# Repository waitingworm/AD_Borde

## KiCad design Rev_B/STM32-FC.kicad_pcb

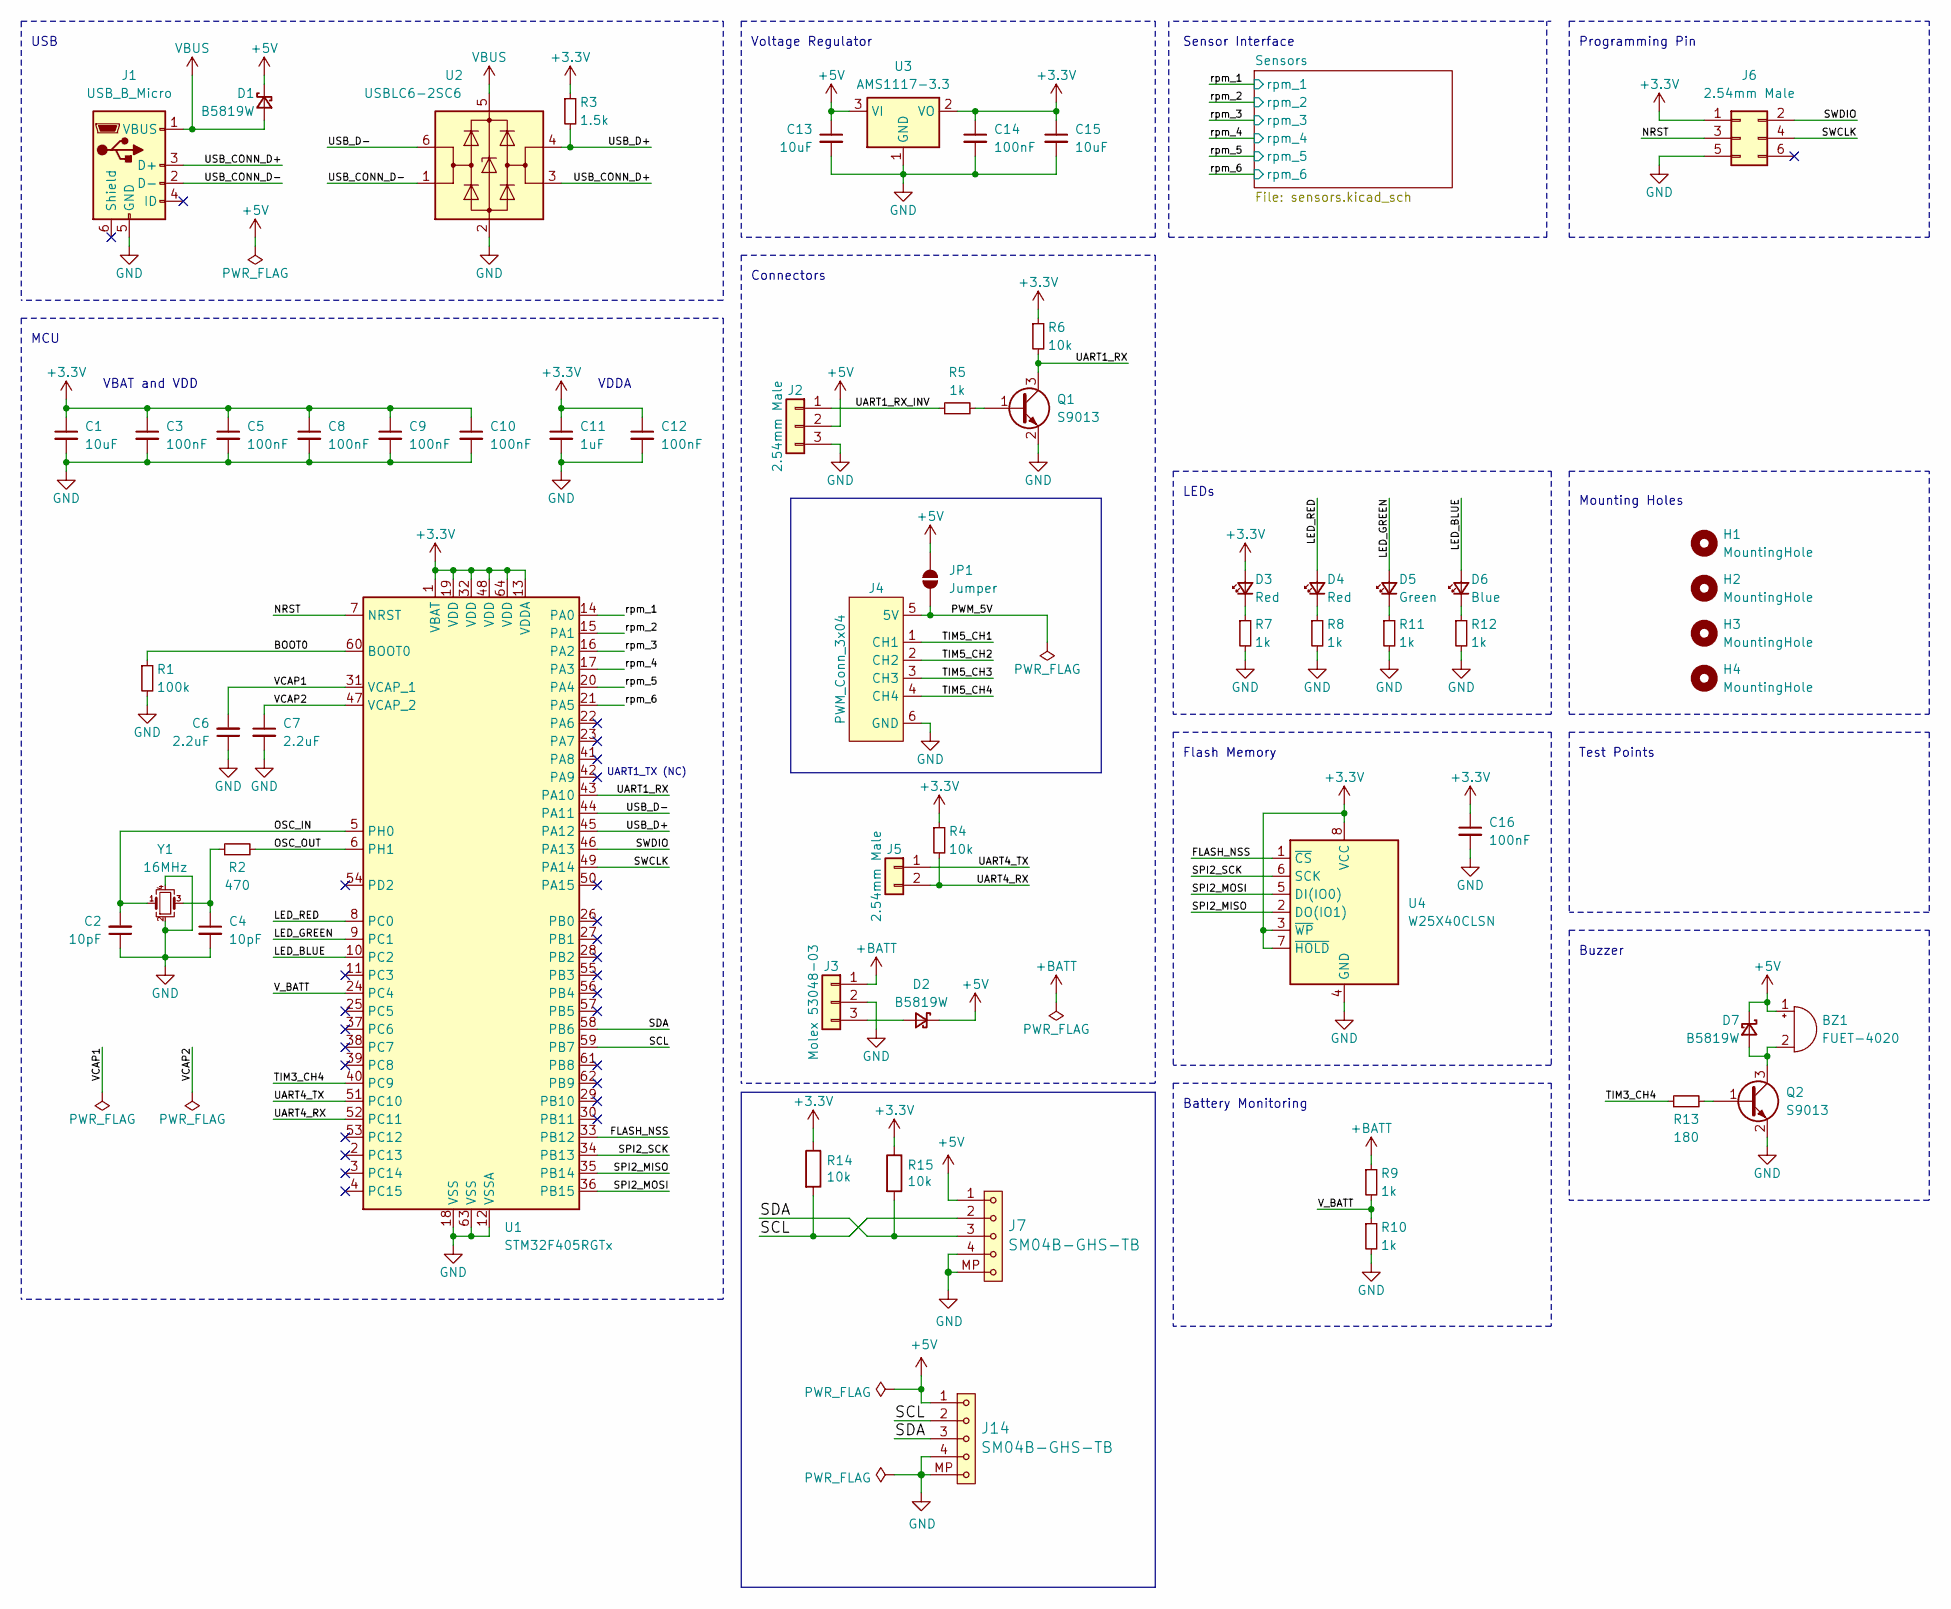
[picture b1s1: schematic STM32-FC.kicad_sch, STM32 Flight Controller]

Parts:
BZ1: FUET-4020
C1: 10uF; C_0402_1005Metric; LCSC C19702
C2, C4: 10pF; C_0402_1005Metric
C3, C5, C8, C9, C10, C12: 100nF; C_0402_1005Metric; LCSC C1525
C6, C7: 2.2uF; C_0402_1005Metric
C11: 1uF; C_0402_1005Metric; LCSC C1525
C13, C15: 10uF; C_0402_1005Metric
C14, C16: 100nF; C_0402_1005Metric
D1, D2: B5819W; D_SOD-123; LCSC C8598
D3, D4: Red; LED_0603_1608Metric
D5: Green; LED_0603_1608Metric
D6: Blue; LED_0603_1608Metric
D7: B5819W; D_SOD-123
H1, H2, H3, H4: MountingHole; MountingHole_3.2mm_M3
J1: USB_B_Micro; USB_Micro-B_Molex-105017-0001
J2: 2.54mm Male; PinHeader_1x03_P2.54mm_Vertical
J3: Molex 53048-03; Molex_PicoBlade_53048-0310_1x03_P1.25mm_Horizontal
J4: PWM_Conn_3x04
J5: 2.54mm Male; PinHeader_1x02_P2.54mm_Vertical
J6: 2.54mm Male; PinHeader_2x03_P2.54mm_Vertical
J7, J14: SM04B-GHS-TB; JST_GH_SM04B-GHS-TB_1x04-1MP_P1.25mm_Horizontal
JP1: Jumper; SolderJumper-2_P1.3mm_Open_TrianglePad1.0x1.5mm
Q1, Q2: S9013; SOT-23-3
R1: 100k; R_0402_1005Metric
R2: 470; R_0402_1005Metric
R3: 1.5k; R_0402_1005Metric
R4, R6: 10k; R_0402_1005Metric
R5, R7, R8, R9, R10, R11, R12: 1k; R_0402_1005Metric
R13: 180; R_0402_1005Metric
R14, R15: 10k; R_0603_1608Metric
U1: STM32F405RGTx; LQFP-64_10x10mm_P0.5mm
U2: USBLC6-2SC6; SOT-23-6
U3: AMS1117-3.3; SOT-223-3_TabPin2; LCSC C6186
U4: W25X40CLSN; SOIC-8_3.9x4.9mm_P1.27mm
Y1: 16MHz; Crystal_SMD_Abracon_ABM8G-4Pin_3.2x2.5mm

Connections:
+3.3V: C1.1, C3.1, C5.1, C8.1, C9.1, C10.1, C11.1, C12.1, C14.1, C15.1, C16.1, D3.2 (A), J6.1, R3.1, R4.1, R6.1, R14.1, R15.1, U1.1 (VBAT), U1.13 (VDDA), U1.19 (VDD), U1.32 (VDD), U1.48 (VDD), U1.64 (VDD), U3.2 (VO), U4.3 (~WP), U4.7 (~HOLD), U4.8 (VCC); also elsewhere on the board
+5V: BZ1.1 (+), C13.1, D1.1 (K), D2.1 (K), D7.1 (K), J2.2, J7.1, J14.1, JP1.2 (B), U3.3 (VI)
+BATT: J3.1, R9.1
/BOOT0: R1.1, U1.60 (BOOT0)
/FLASH_NSS: U1.33 (PB12), U4.1 (~CS)
/LED_BLUE: D6.2 (A), U1.10 (PC2)
/LED_GREEN: D5.2 (A), U1.9 (PC1)
/LED_RED: D4.2 (A), U1.8 (PC0)
/NRST: J6.3, U1.7 (NRST)
/OSC_IN: C2.2, U1.5 (PH0), Y1.1
/OSC_OUT: R2.2, U1.6 (PH1)
/PWM_5V: J4.5 (5V), JP1.1 (A)
/SCL: J7.2, J14.2, R14.2, U1.59 (PB7)
/SDA: J7.3, J14.3, R15.2, U1.58 (PB6)
/SPI2_MISO: U1.35 (PB14), U4.2 (DO(IO1))
/SPI2_MOSI: U1.36 (PB15), U4.5 (DI(IO0))
/SPI2_SCK: U1.34 (PB13), U4.6 (SCK)
/SWCLK: J6.4, U1.49 (PA14)
/SWDIO: J6.2, U1.46 (PA13)
/TIM3_CH4: R13.1, U1.40 (PC9)
/TIM5_CH1: J4.1 (CH1)
/TIM5_CH2: J4.2 (CH2)
/TIM5_CH3: J4.3 (CH3)
/TIM5_CH4: J4.4 (CH4)
/UART1_RX: Q1.3 (C), R6.2, U1.43 (PA10)
/UART1_RX_INV: J2.1, R5.1
/UART4_RX: J5.2, R4.2, U1.52 (PC11)
/UART4_TX: J5.1, U1.51 (PC10)
/USB_CONN_D+: J1.3 (D+), U2.3 (I/O2)
/USB_CONN_D-: J1.2 (D-), U2.1 (I/O1)
/USB_D+: R3.2, U1.45 (PA12), U2.4 (I/O2)
/USB_D-: U1.44 (PA11), U2.6 (I/O1)
/VCAP1: C6.2, U1.31 (VCAP_1)
/VCAP2: C7.1, U1.47 (VCAP_2)
/V_BATT: R9.2, R10.1, U1.24 (PC4)
/rpm_1: U1.14 (PA0); also elsewhere on the board
/rpm_2: U1.15 (PA1); also elsewhere on the board
/rpm_3: U1.16 (PA2); also elsewhere on the board
/rpm_4: U1.17 (PA3); also elsewhere on the board
/rpm_5: U1.20 (PA4); also elsewhere on the board
/rpm_6: U1.21 (PA5); also elsewhere on the board
GND: C1.2, C2.1, C3.2, C4.2, C5.2, C6.1, C7.2, C8.2, C9.2, C10.2, C11.2, C12.2, C13.2, C14.2, C15.2, C16.2, J1.5 (GND), J2.3, J3.2, J4.6 (GND), J6.5, J7.4, J7.MP, J14.4, J14.MP, Q1.2 (E), Q2.2 (E), R1.2, R7.2, R8.2, R10.2, R11.2, R12.2, U1.12 (VSSA), U1.18 (VSS), U1.63 (VSS), U2.2 (GND), U3.1 (GND), U4.4 (GND), Y1.2, Y1.4; also elsewhere on the board
unnamed: BZ1.2 (-), D7.2 (A), Q2.3 (C)
unnamed: C4.1, R2.1, Y1.3
unnamed: D2.2 (A), J3.3
unnamed: D3.1 (K), R7.1
unnamed: D4.1 (K), R8.1
unnamed: D5.1 (K), R11.1
unnamed: D6.1 (K), R12.1
unnamed: Q1.1 (B), R5.2
unnamed: Q2.1 (B), R13.2
VBUS: D1.2 (A), J1.1 (VBUS), U2.5 (VBUS)

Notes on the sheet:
Connectors
Voltage Regulator
Test Points
UART1_TX (NC)
LEDs
Sensor Interface
MCU
VDDA
Battery Monitoring
Buzzer
Programming Pin
USB
Flash Memory
VBAT and VDD
Mounting Holes

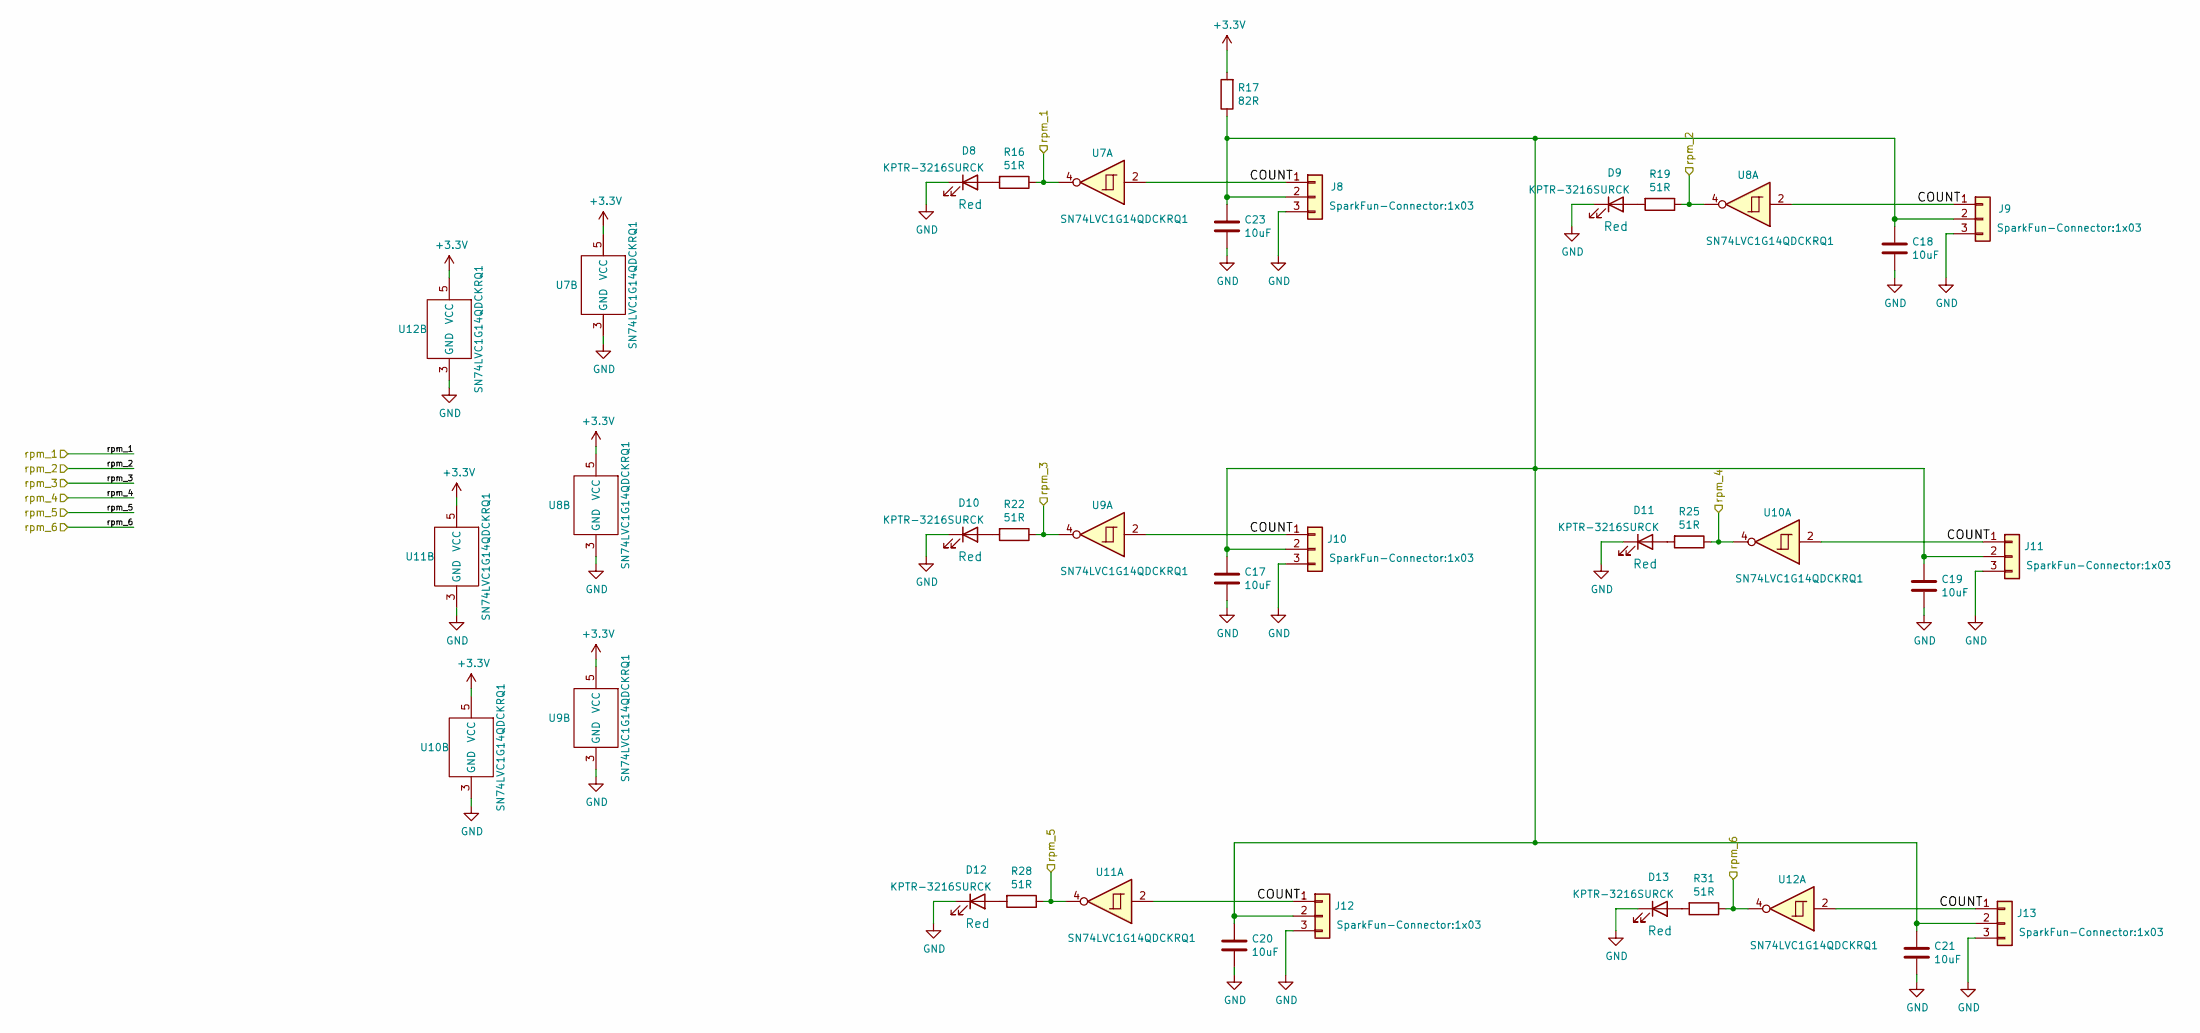
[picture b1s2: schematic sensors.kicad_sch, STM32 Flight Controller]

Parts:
C17, C18, C19, C20, C21, C23: 10uF; C_0603_1608Metric
D8, D9, D10, D11, D12, D13: KPTR-3216SURCK; LED_1206_mill
J8, J9, J10, J11, J12, J13: Conn_01x03; 1x03
R16, R19, R22, R25, R28, R31: 51R; R_0603_1608Metric
R17: 82R; R_0805_2012Metric
U7, U8, U9, U10, U11, U12: SN74LVC1G14QDCKRQ1; SOT-353_SC-70-5

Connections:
+3.3V: R17.2, U7.5 (VCC), U8.5 (VCC), U9.5 (VCC), U10.5 (VCC), U11.5 (VCC), U12.5 (VCC); also elsewhere on the board
/Sensors/COUNT: J8.1, J9.1, J10.1, J11.1, J12.1, J13.1, U7.2, U8.2, U9.2, U10.2, U11.2, U12.2
/rpm_1: R16.1, U7.4; also elsewhere on the board
/rpm_2: R19.1, U8.4; also elsewhere on the board
/rpm_3: R22.1, U9.4; also elsewhere on the board
/rpm_4: R25.1, U10.4; also elsewhere on the board
/rpm_5: R28.1, U11.4; also elsewhere on the board
/rpm_6: R31.1, U12.4; also elsewhere on the board
GND: C17.2, C18.2, C19.2, C20.2, C21.2, C23.2, D8.1 (K), D9.1 (K), D10.1 (K), D11.1 (K), D12.1 (K), D13.1 (K), J8.3, J9.3, J10.3, J11.3, J12.3, J13.3, U7.3 (GND), U8.3 (GND), U9.3 (GND), U10.3 (GND), U11.3 (GND), U12.3 (GND); also elsewhere on the board
unnamed: D8.2 (A), R16.2
unnamed: D9.2 (A), R19.2
unnamed: D10.2 (A), R22.2
unnamed: D11.2 (A), R25.2
unnamed: D12.2 (A), R28.2
unnamed: D13.2 (A), R31.2
unnamed: C17.1, C18.1, C19.1, C20.1, C21.1, C23.1, J8.2, J9.2, J10.2, J11.2, J12.2, J13.2, R17.1

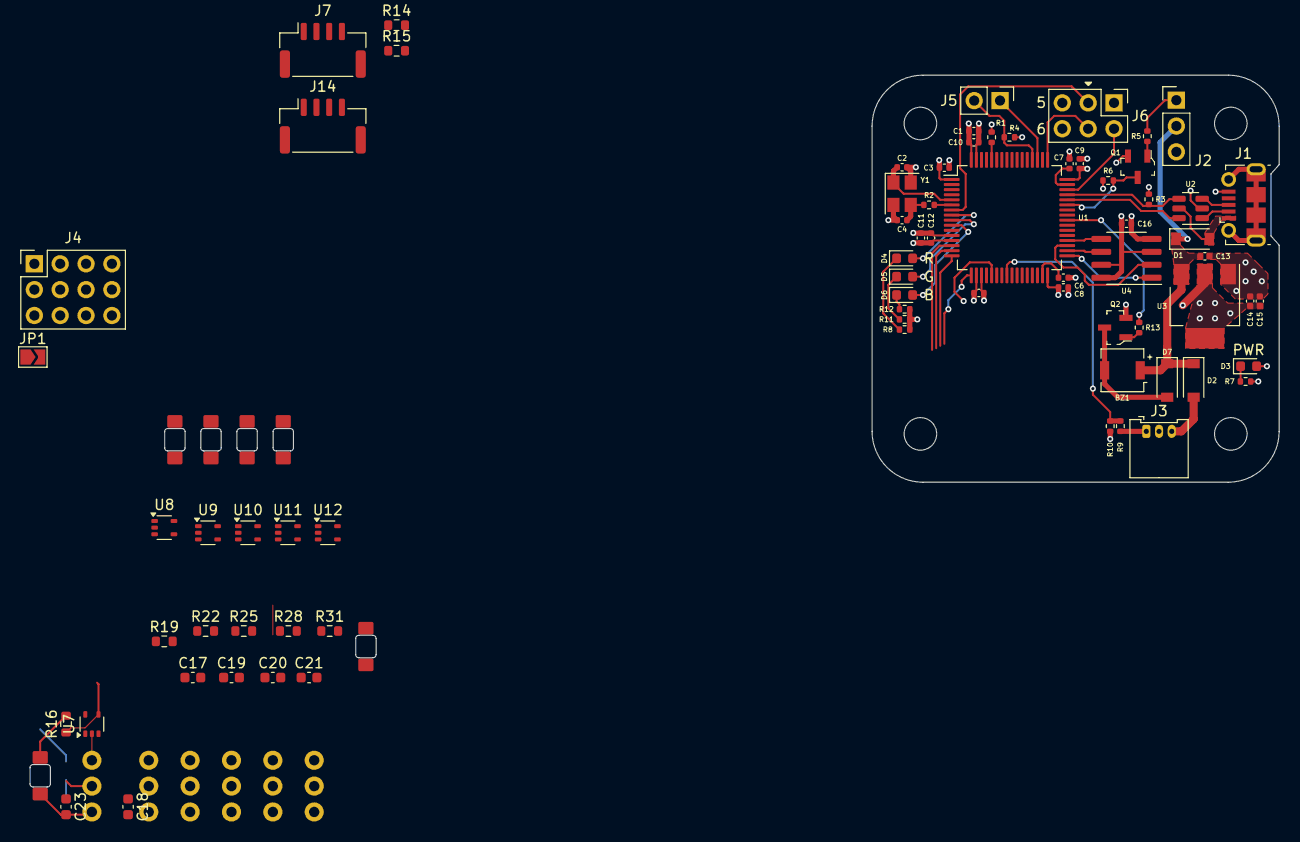
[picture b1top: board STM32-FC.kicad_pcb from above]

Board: 4 copper layers, 122.7 x 69.9 mm, 90 parts (1 on the bottom side), 56 nets.
